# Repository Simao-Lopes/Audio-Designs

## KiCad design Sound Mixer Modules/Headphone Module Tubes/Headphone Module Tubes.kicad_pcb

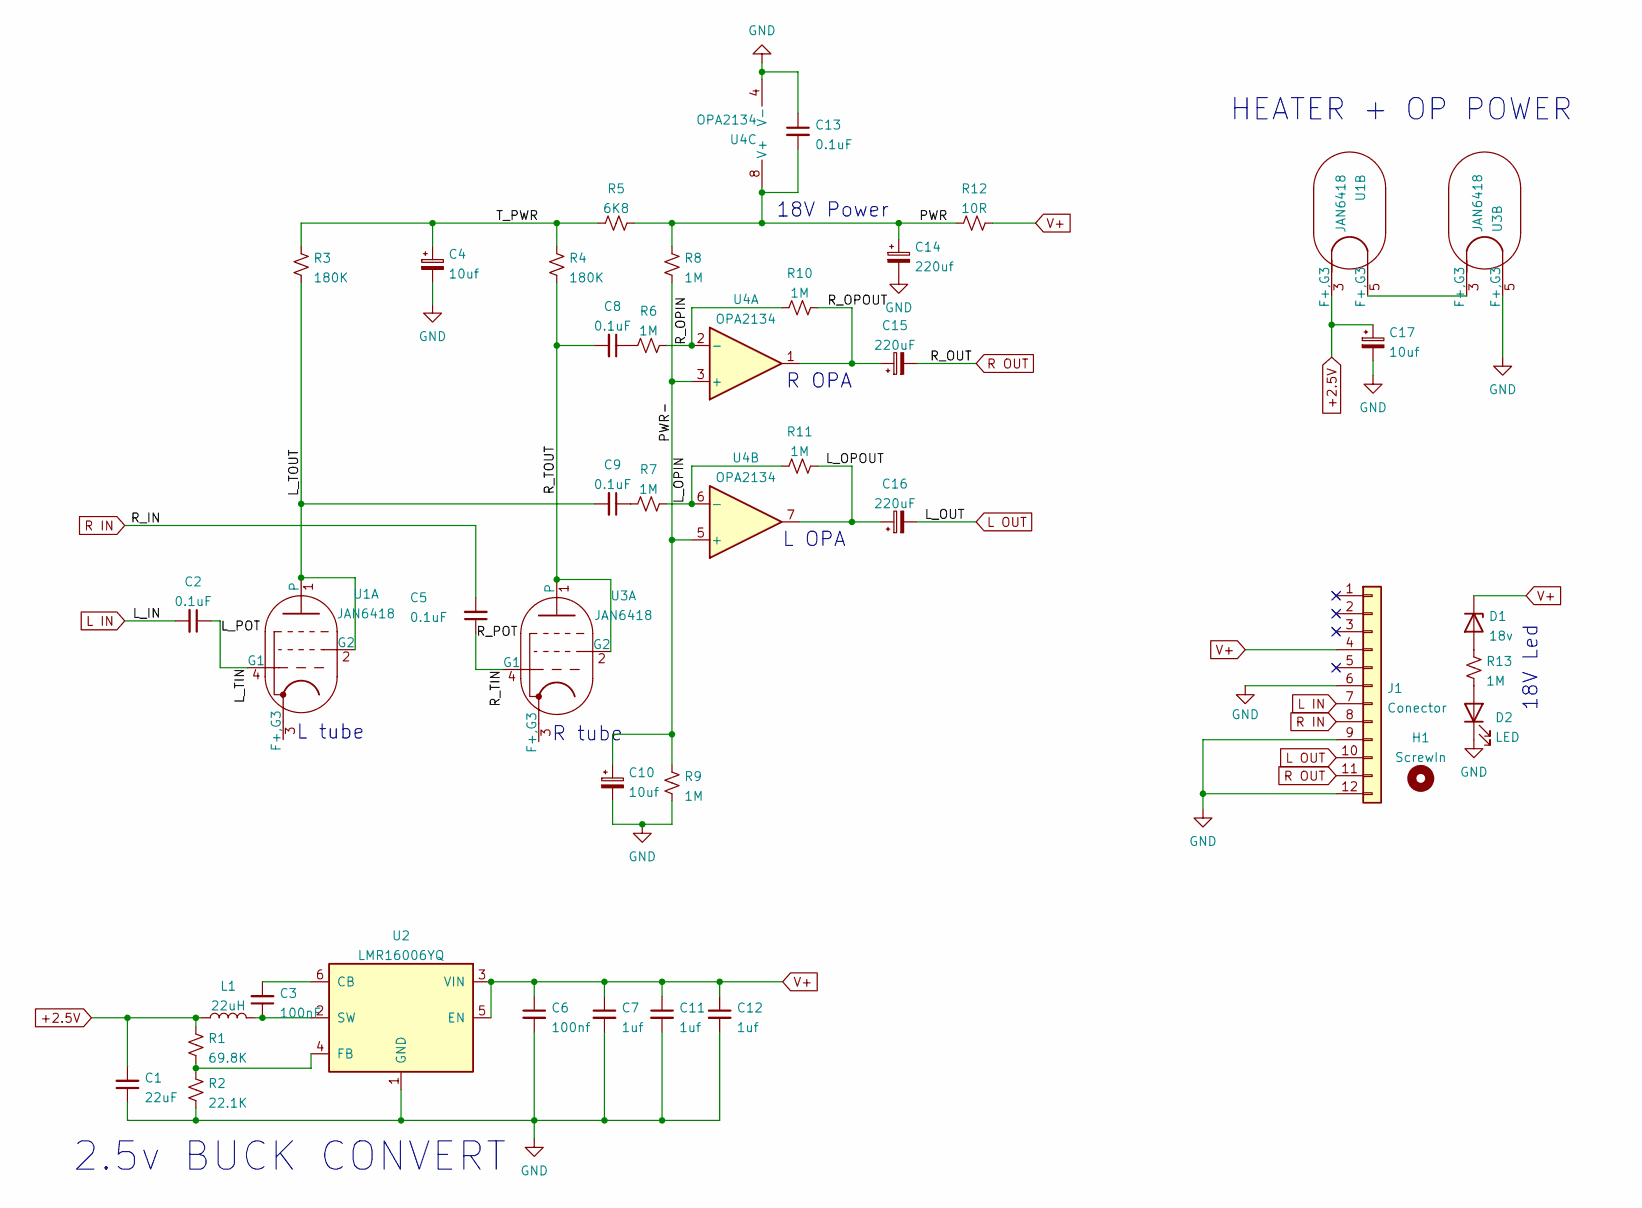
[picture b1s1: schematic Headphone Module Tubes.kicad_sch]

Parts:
C1: 22uF; C_0603_1608Metric_Pad1.08x0.95mm_HandSolder
C2, C5, C8, C9: 0.1uF; C_Rect_L7.2mm_W7.2mm_P5.00mm_FKS2_FKP2_MKS2_MKP2
C3: 100nF; C_0402_1005Metric_Pad0.74x0.62mm_HandSolder
C4, C10, C17: 10uf; CP_Radial_D5.0mm_P2.50mm
C6: 100nf; C_0603_1608Metric_Pad1.08x0.95mm_HandSolder
C7, C11, C12: 1uf; C_0603_1608Metric_Pad1.08x0.95mm_HandSolder
C13: 0.1uF; C_Rect_L7.2mm_W3.5mm_P5.00mm_FKS2_FKP2_MKS2_MKP2
C14: 220uf; CP_Radial_D10.0mm_P5.00mm_P7.50mm
C15, C16: 220uF; CP_Radial_D10.0mm_P5.00mm_P7.50mm
D1: 18v; D_1206_3216Metric_Pad1.42x1.75mm_HandSolder
D2: LED; LED_1206_3216Metric_Pad1.42x1.75mm_HandSolder
H1: ScrewIn; MountingHole_3.2mm_M3
J1: Conector; PinHeader_2x12_P2.54mm_Vertical
L1: 22uH; L_Bourns_SDR1806
R1: 69.8K; R_0402_1005Metric_Pad0.72x0.64mm_HandSolder
R2: 22.1K; R_0402_1005Metric_Pad0.72x0.64mm_HandSolder
R3, R4: 180K; R_1206_3216Metric_Pad1.30x1.75mm_HandSolder
R5: 6K8; R_1206_3216Metric_Pad1.30x1.75mm_HandSolder
R6, R7, R8, R9, R10, R11, R13: 1M; R_1206_3216Metric_Pad1.30x1.75mm_HandSolder
R12: 10R; R_1206_3216Metric_Pad1.30x1.75mm_HandSolder
U1, U3: JAN6418; Valve_Mini_Pentode_Linear
U2: LMR16006YQ; SOT-23-6
U4: OPA2134; DIP-8_W7.62mm

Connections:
+2.5V: C1.2, C17.1, L1.1, R1.1, U1.3 (F+,G3)
/L_OPIN: R7.2, R11.1, U4.6 (-)
/L_OPOUT: C16.1, R11.2, U4.7
/L_POT: C2.1, U1.4 (G1)
/L_TOUT: C9.2, R3.1, U1.1, U1.2 (G2)
/PWR: C13.2, C14.1, R5.1, R8.2, R12.2, U4.8 (V+)
/PWR-: C10.1, R8.1, R9.1, U4.3 (+), U4.5 (+)
/R_OPIN: R6.2, R10.1, U4.2 (-)
/R_OPOUT: C15.1, R10.2, U4.1
/R_POT: C5.1, U3.4 (G1)
/R_TOUT: C8.2, R4.1, U3.1, U3.2 (G2)
/T_PWR: C4.1, R3.2, R4.2, R5.2
L IN: C2.2, J1.7
L OUT: C16.2, J1.10
unnamed: C3.1, L1.2, U2.2 (SW)
unnamed: C3.2, U2.6 (CB)
unnamed: C8.1, R6.1
unnamed: C9.1, R7.1
unnamed: D1.2 (A), R13.2
unnamed: D2.2 (A), R13.1
unnamed: R1.2, R2.1, U2.4 (FB)
unnamed: U1.5 (F+,G3), U3.3 (F+,G3)
R IN: C5.2, J1.8
R OUT: C15.2, J1.11
V+: C6.1, C7.1, C11.1, C12.1, D1.1 (K), J1.4, R12.1, U2.3 (VIN), U2.5 (EN)

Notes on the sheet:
R tube
2.5v BUCK CONVERT
HEATER + OP POWER
L OPA
L tube
18V Led
R OPA
18V Power

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
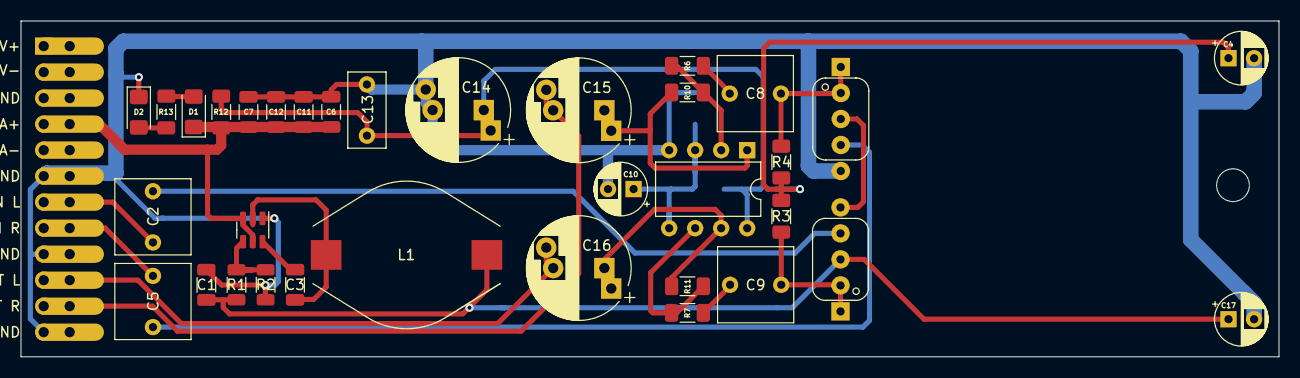
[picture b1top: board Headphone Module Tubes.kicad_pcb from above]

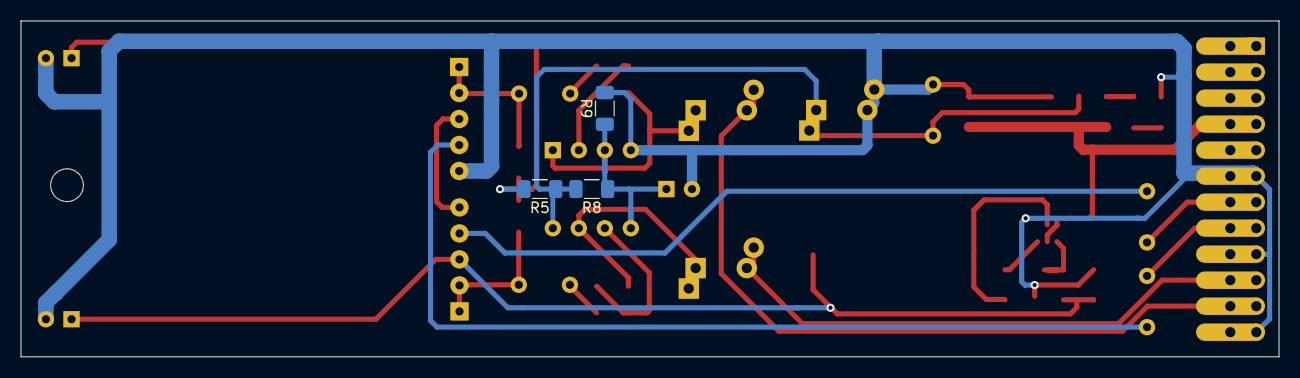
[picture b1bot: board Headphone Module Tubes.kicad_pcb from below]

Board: 2 copper layers, 122.9 x 32.8 mm, 39 parts (3 on the bottom side), 26 nets.

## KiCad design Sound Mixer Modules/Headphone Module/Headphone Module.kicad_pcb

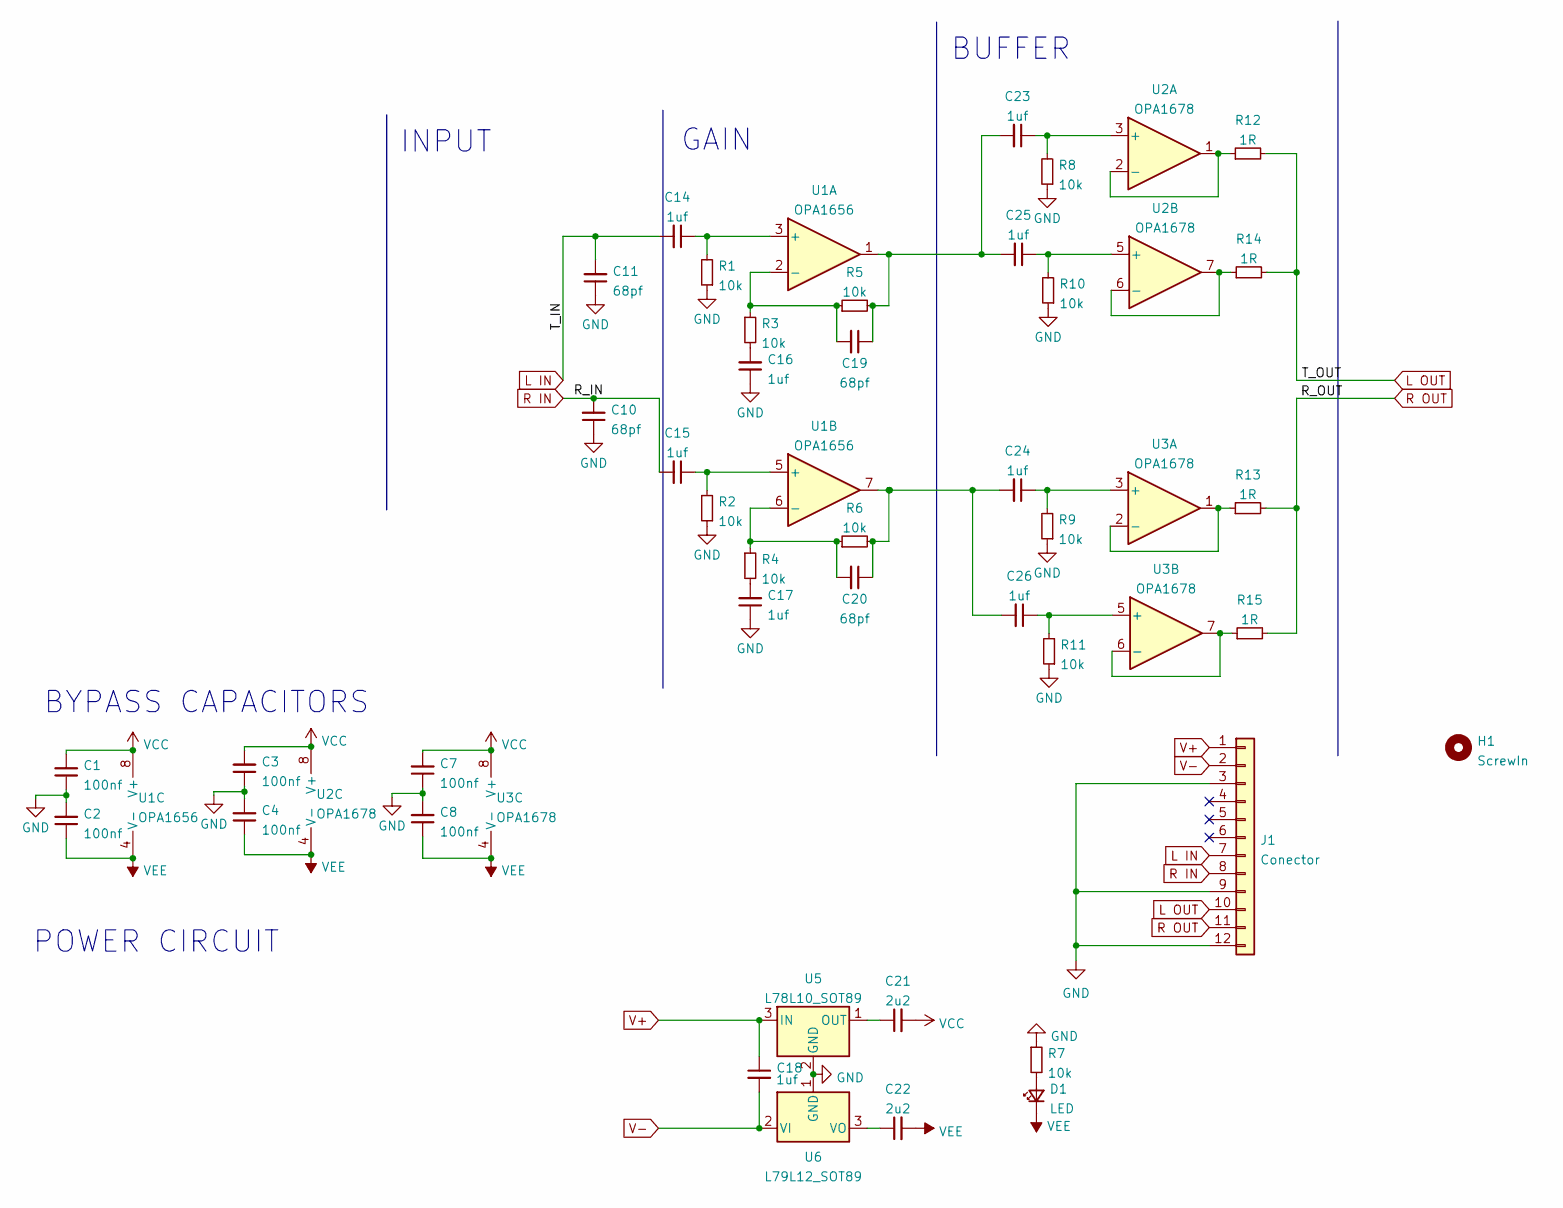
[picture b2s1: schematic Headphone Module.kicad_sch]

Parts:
C1, C2, C3, C4, C7, C8: 100nf; C_1206_3216Metric_Pad1.33x1.80mm_HandSolder
C10, C11, C19, C20: 68pf; C_1206_3216Metric_Pad1.33x1.80mm_HandSolder
C14, C15, C16, C17, C18, C23, C24, C25, C26: 1uf; C_1206_3216Metric_Pad1.33x1.80mm_HandSolder
C21, C22: 2u2; C_1206_3216Metric_Pad1.33x1.80mm_HandSolder
D1: LED; D_0201_0603Metric_Pad0.64x0.40mm_HandSolder
H1: ScrewIn; MountingHole_3.2mm_M3
J1: Conector; PinHeader_2x12_P2.54mm_Vertical
R1, R2, R3, R4, R5, R6, R7, R8, R9, R10, R11: 10k; R_0603_1608Metric_Pad0.98x0.95mm_HandSolder
R12, R13, R14, R15: 1R; R_0603_1608Metric_Pad0.98x0.95mm_HandSolder
U1: OPA1656; SOIC-8-1EP_3.9x4.9mm_P1.27mm_EP2.29x3mm
U2, U3: OPA1678; SOIC-8-1EP_3.9x4.9mm_P1.27mm_EP2.29x3mm
U5: L78L10_SOT89; SOT-89-3
U6: L79L12_SOT89; SOT-89-3

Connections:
GND: C1.1, C2.2, C3.1, C4.2, C7.1, C8.2, C10.1, C11.1, C16.1, C17.1, J1.3, J1.9, J1.12, R1.1, R2.1, R7.1, R8.1, R9.1, R10.1, R11.1, U5.2 (GND), U6.1 (GND)
L IN: C11.2, C14.2, J1.7
L OUT: J1.10, R12.2, R14.2
unnamed: C14.1, R1.2, U1.3 (+)
unnamed: C15.1, R2.2, U1.5 (+)
unnamed: C16.2, R3.2
unnamed: C17.2, R4.2
unnamed: C19.1, C23.2, C25.2, R5.2, U1.1
unnamed: C19.2, R3.1, R5.1, U1.2 (-)
unnamed: C20.1, R6.2, U1.7
unnamed: C20.2, R4.1, R6.1, U1.6 (-)
unnamed: C21.1, U5.1 (OUT)
unnamed: C22.1, U6.3 (VO)
unnamed: C23.1, R8.2, U2.3 (+)
unnamed: C24.1, R9.2, U3.3 (+)
unnamed: C24.2, C26.2
unnamed: C25.1, R10.2, U2.5 (+)
unnamed: C26.1, R11.2, U3.5 (+)
unnamed: D1.2 (A), R7.2
unnamed: R12.1, U2.1, U2.2 (-)
unnamed: R13.1, U3.1, U3.2 (-)
unnamed: R14.1, U2.6 (-), U2.7
unnamed: R15.1, U3.6 (-), U3.7
R IN: C10.2, C15.2, J1.8
R OUT: J1.11, R13.2, R15.2
V+: C18.1, J1.1, U5.3 (IN)
V-: C18.2, J1.2, U6.2 (VI)
VCC: C1.2, C3.2, C7.2, C21.2, U1.8 (V+), U2.8 (V+), U3.8 (V+)
VEE: C2.1, C4.1, C8.1, C22.2, D1.1 (K), U1.4 (V-), U2.4 (V-), U3.4 (V-)

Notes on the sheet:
INPUT
POWER CIRCUIT
GAIN
BUFFER
BYPASS CAPACITORS

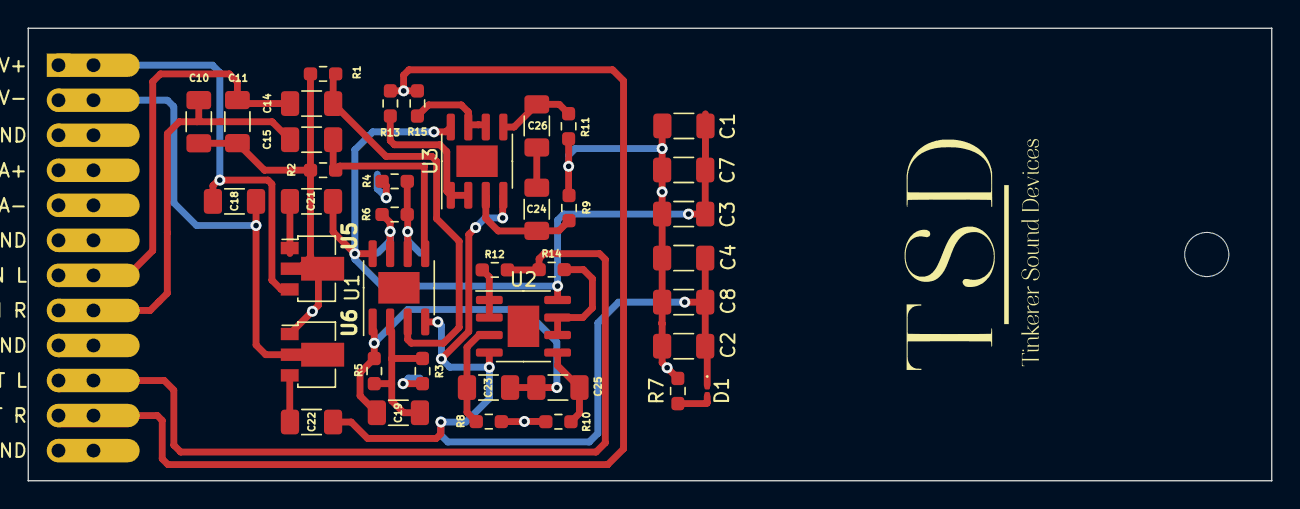
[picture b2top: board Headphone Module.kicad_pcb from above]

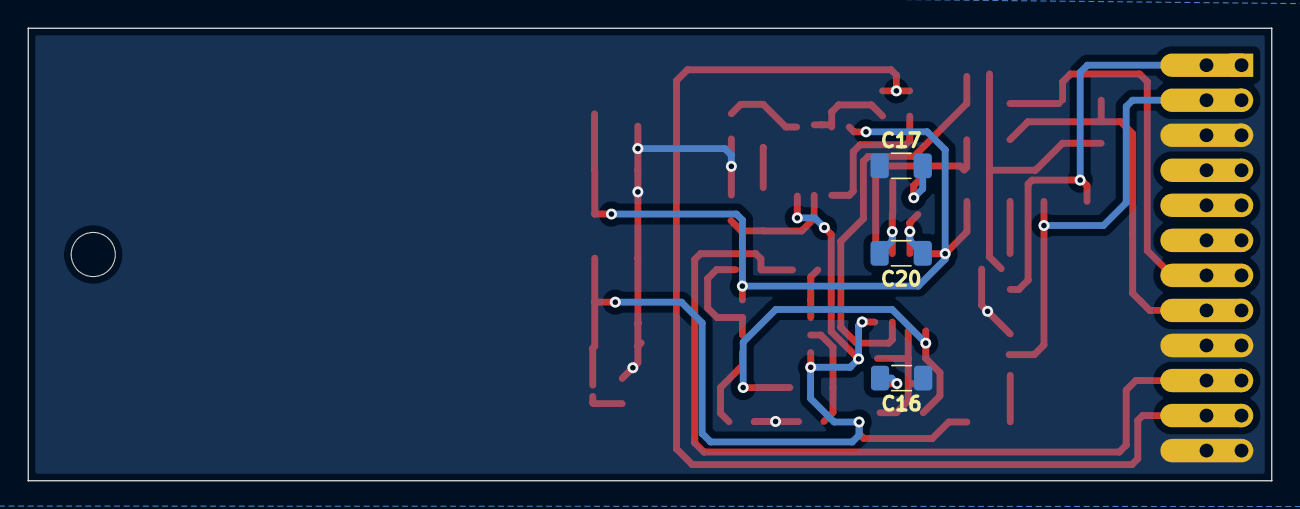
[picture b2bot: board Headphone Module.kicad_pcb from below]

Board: 2 copper layers, 90.1 x 32.8 mm, 44 parts (3 on the bottom side), 29 nets.

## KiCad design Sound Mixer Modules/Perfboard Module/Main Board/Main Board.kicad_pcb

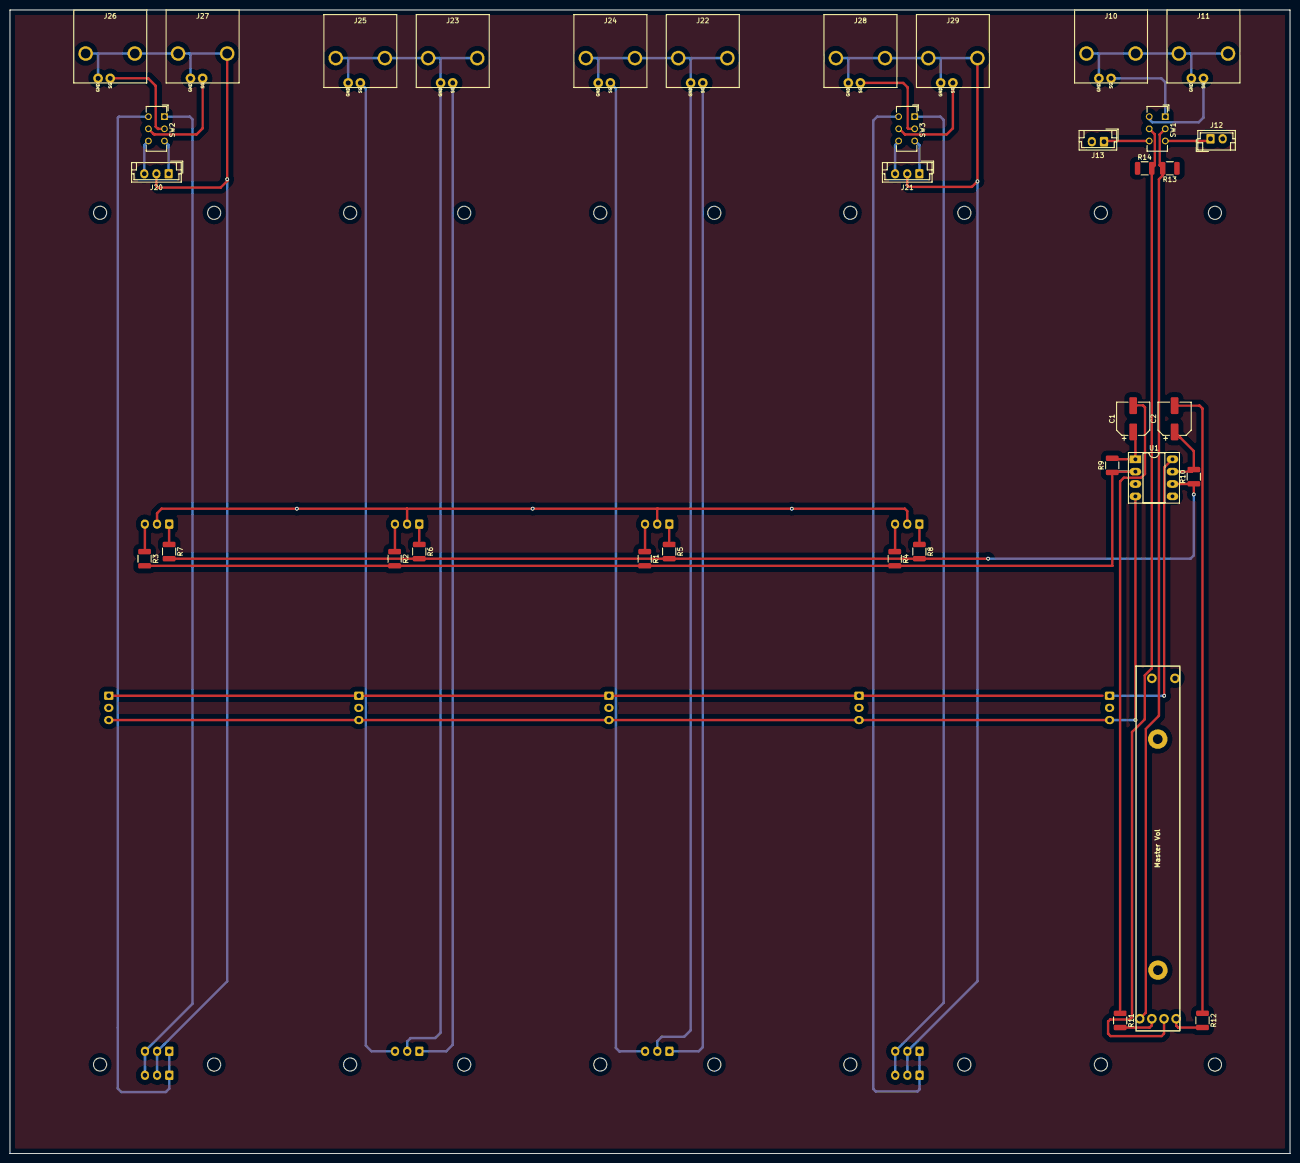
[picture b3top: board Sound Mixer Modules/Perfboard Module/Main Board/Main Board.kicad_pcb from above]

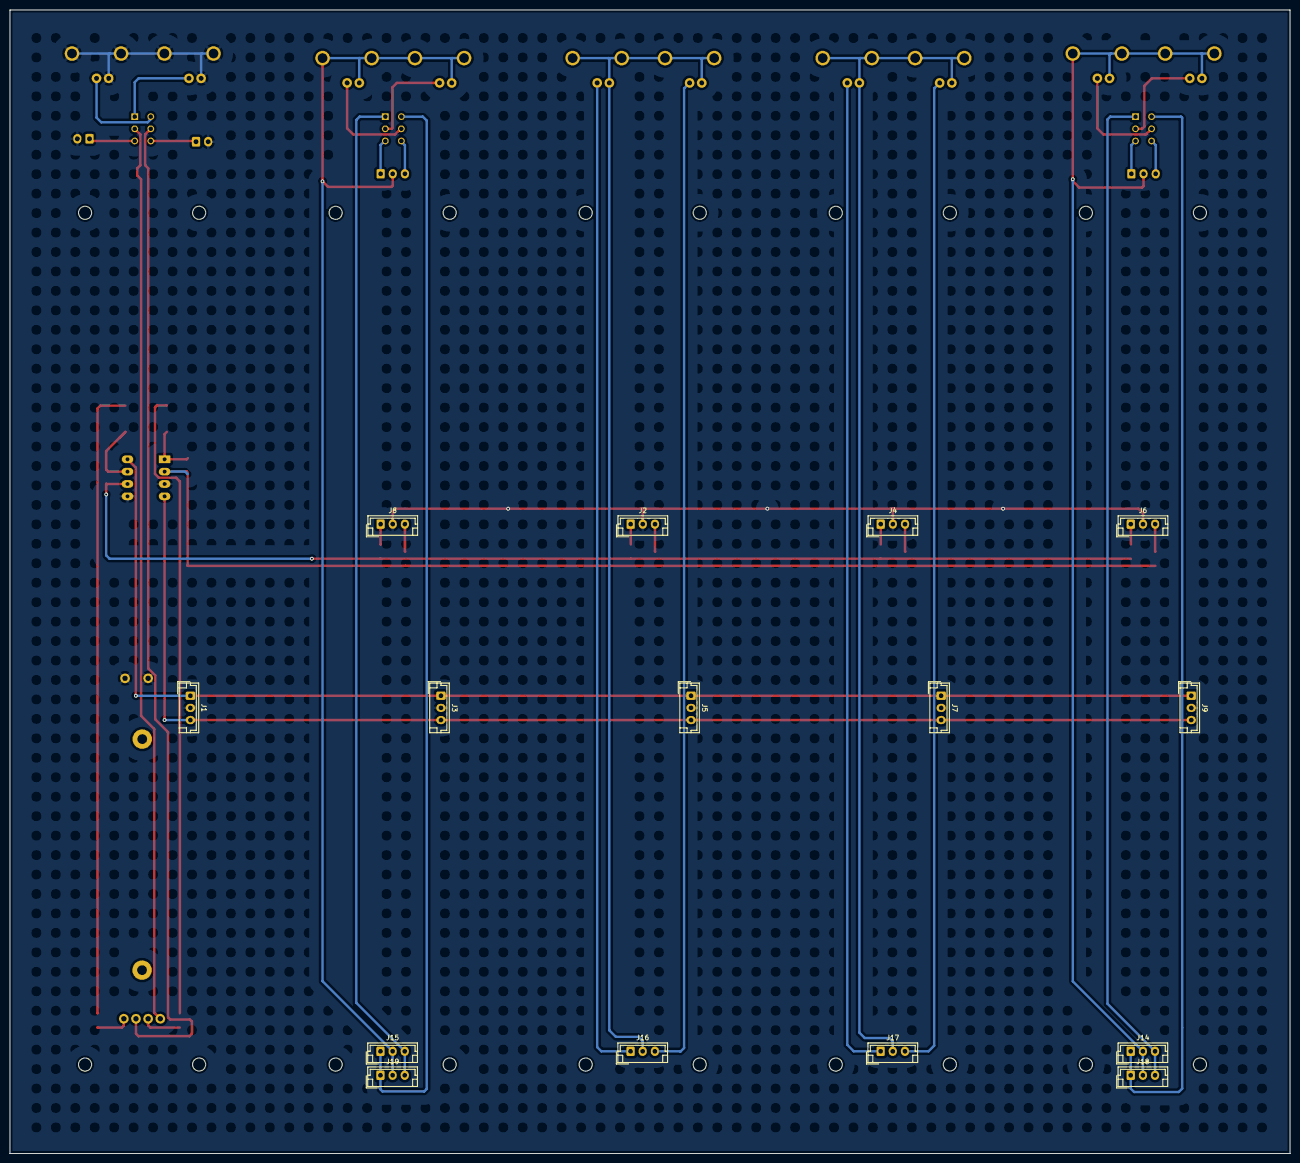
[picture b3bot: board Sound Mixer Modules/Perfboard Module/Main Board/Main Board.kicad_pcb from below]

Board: 2 copper layers, 263.2 x 235.1 mm, 50 parts (15 on the bottom side), 45 nets.

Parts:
C1, C2: 10Uf; CP_Elec_6.3x5.4_Nichicon
J1: Power mix; JST_EH_B3B-EH-A_1x03_P2.50mm_Vertical
J2: OUT1; JST_EH_B3B-EH-A_1x03_P2.50mm_Vertical
J3: Power1; JST_EH_B3B-EH-A_1x03_P2.50mm_Vertical
J4: OUT2; JST_EH_B3B-EH-A_1x03_P2.50mm_Vertical
J5: Power2; JST_EH_B3B-EH-A_1x03_P2.50mm_Vertical
J6: OUT3; JST_EH_B3B-EH-A_1x03_P2.50mm_Vertical
J7: Power3; JST_EH_B3B-EH-A_1x03_P2.50mm_Vertical
J8: OUT4; JST_EH_B3B-EH-A_1x03_P2.50mm_Vertical
J9: Power4; JST_EH_B3B-EH-A_1x03_P2.50mm_Vertical
J10: L_RCA; RCA PANEL 2PIN FOOTPRINT
J11, J22, J23, J24, J25, J26, J27, J28, J29: R_RCA; RCA PANEL 2PIN FOOTPRINT
J12: L_Amp; JST_EH_B2B-EH-A_1x02_P2.50mm_Vertical
J13: R_Amp; JST_EH_B2B-EH-A_1x02_P2.50mm_Vertical
J14: IN3; JST_EH_B3B-EH-A_1x03_P2.50mm_Vertical
J15: IN4; JST_EH_B3B-EH-A_1x03_P2.50mm_Vertical
J16: IN1; JST_EH_B3B-EH-A_1x03_P2.50mm_Vertical
J17: IN2; JST_EH_B3B-EH-A_1x03_P2.50mm_Vertical
J18: Phono In1; JST_EH_B3B-EH-A_1x03_P2.50mm_Vertical
J19: Phono In2; JST_EH_B3B-EH-A_1x03_P2.50mm_Vertical
J20: Phono out1; JST_EH_B3B-EH-A_1x03_P2.50mm_Vertical
J21: Phono out2; JST_EH_B3B-EH-A_1x03_P2.50mm_Vertical
R1, R2, R3, R4, R5, R6, R7, R8, R9, R10: 10K; R_1210_3225Metric
R11, R12: 100; R_1210_3225Metric
R13, R14: 15K; R_1210_3225Metric
RV1: Master Vol; ALPS RS60112
SW1: SW_DPDT_x2; SW_CuK_JS202011CQN_DPDT_Straight
SW2: IN3 SW; SW_CuK_JS202011CQN_DPDT_Straight
SW3: IN4 SW; SW_CuK_JS202011CQN_DPDT_Straight
U1: NE5532; DIP-8_W7.62mm_Socket_LongPads

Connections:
GND: J1.2, J2.2, J3.2, J4.2, J5.2, J6.2, J7.2, J8.2, J9.2, J10.2 (Ext), J11.2 (Ext), J12.2, J13.2, R13.1, R14.1, RV1.3, RV1.6, U1.3 (+), U1.5 (+)
L1: J2.3, R1.1
L2: J4.3, R2.1
L3: J6.3, R3.1
L4: J8.3, R4.1
unnamed: C1.1, R9.2, U1.1
unnamed: C1.2, R11.1
unnamed: C2.1, R10.2, U1.7
unnamed: C2.2, R12.1
unnamed: J1.1, J3.1, J5.1, J7.1, J9.1, U1.8 (V+)
unnamed: J1.3, J3.3, J5.3, J7.3, J9.3, U1.4 (V-)
unnamed: J10.1 (In), SW1.1 (A)
unnamed: J11.1 (In), SW1.4 (A)
unnamed: J12.1, SW1.3 (C)
unnamed: J13.1, SW1.6 (C)
unnamed: J14.1, J18.1, SW2.4 (A)
unnamed: J14.2, J18.2, J20.2, J26.2 (Ext), J27.2 (Ext)
unnamed: J14.3, J18.3, SW2.1 (A)
unnamed: J15.1, J19.1, SW3.4 (A)
unnamed: J15.2, J19.2, J21.2, J28.2 (Ext), J29.2 (Ext)
unnamed: J15.3, J19.3, SW3.1 (A)
unnamed: J16.1, J22.1 (In)
unnamed: J16.2, J22.2 (Ext)
unnamed: J16.3, J24.1 (In)
unnamed: J17.1, J23.1 (In)
unnamed: J17.2, J23.2 (Ext), J25.2 (Ext)
unnamed: J17.3, J25.1 (In)
unnamed: J20.1, SW2.3 (C)
unnamed: J20.3, SW2.6 (C)
unnamed: J21.1, SW3.3 (C)
unnamed: J21.3, SW3.6 (C)
unnamed: J26.1 (In), SW2.2 (B)
unnamed: J27.1 (In), SW2.5 (B)
unnamed: J28.1 (In), SW3.2 (B)
unnamed: J29.1 (In), SW3.5 (B)
unnamed: R1.2, R2.2, R3.2, R4.2, R9.1, U1.2 (-)
unnamed: R5.2, R6.2, R7.2, R8.2, R10.1, U1.6 (-)
unnamed: R11.2, RV1.1
unnamed: R12.2, RV1.4
unnamed: R13.2, RV1.2, SW1.2 (B)
unnamed: R14.2, RV1.5, SW1.5 (B)
R1: J2.1, R5.1
R2: J4.1, R6.1
R3: J6.1, R7.1
R4: J8.1, R8.1

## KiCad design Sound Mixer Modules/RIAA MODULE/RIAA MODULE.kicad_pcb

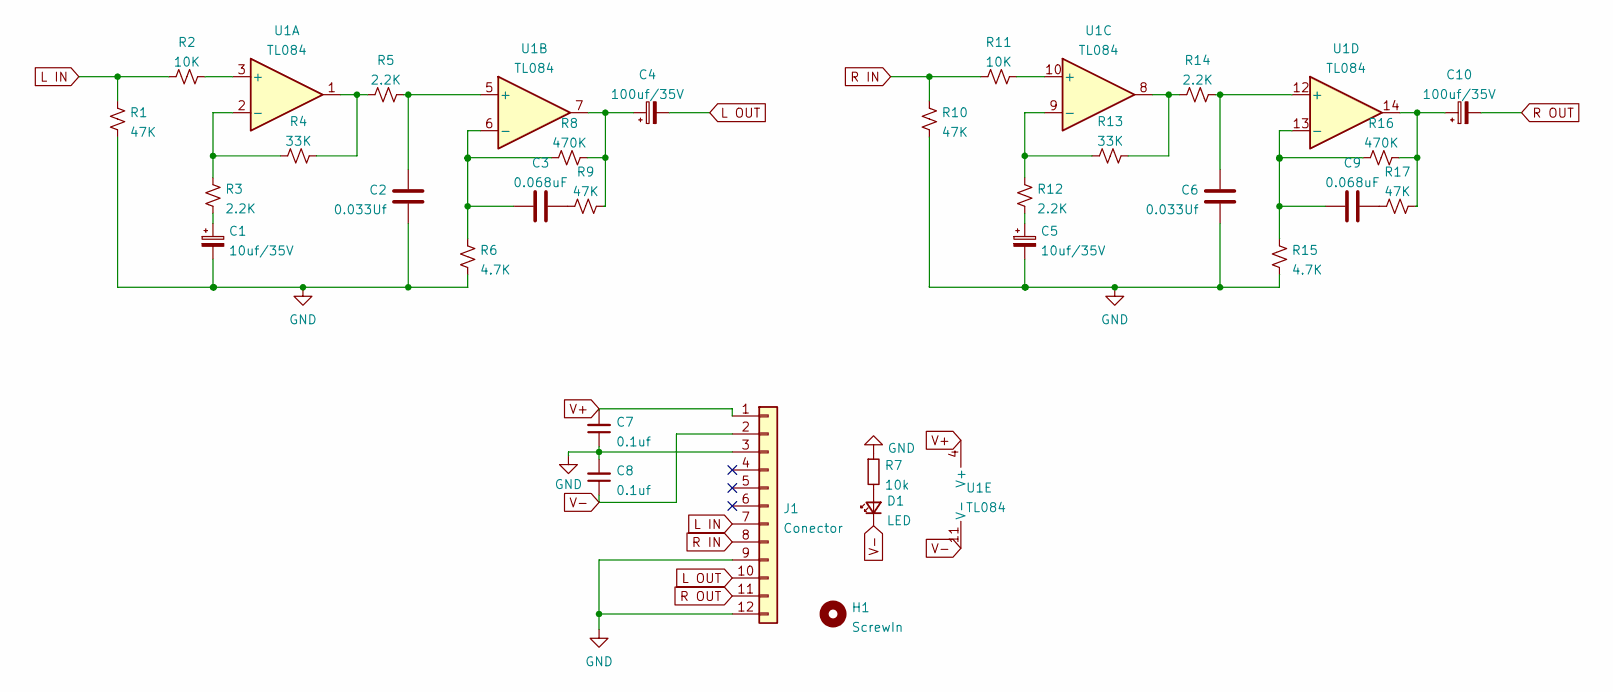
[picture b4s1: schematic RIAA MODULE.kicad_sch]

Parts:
C1, C5: 10uf/35V; CP_Elec_6.3x5.4_Nichicon
C2, C6: 0.033Uf; C_1206_3216Metric_Pad1.33x1.80mm_HandSolder
C3, C9: 0.068uF; C_1206_3216Metric_Pad1.33x1.80mm_HandSolder
C4, C10: 100uf/35V; CP_Elec_6.3x5.4_Nichicon
C7, C8: 0.1uf; C_1206_3216Metric_Pad1.33x1.80mm_HandSolder
D1: LED; D_0201_0603Metric_Pad0.64x0.40mm_HandSolder
H1: ScrewIn; MountingHole_3.2mm_M3
J1: Conector; PinHeader_2x12_P2.54mm_Vertical
R1, R9, R10, R17: 47K; R_1206_3216Metric
R2, R11: 10K; R_1206_3216Metric
R3, R5, R12, R14: 2.2K; R_1206_3216Metric
R4, R13: 33K; R_1206_3216Metric
R6, R15: 4.7K; R_1206_3216Metric
R7: 10k; R_1206_3216Metric
R8, R16: 470K; R_1206_3216Metric
U1: TL084; DIP-14_W7.62mm_Socket_LongPads

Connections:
GND: C2.2, C6.2, C7.1, C8.2, J1.3, J1.9, J1.12, R6.1, R7.1, R15.1
L IN: J1.7, R1.2, R2.1
L OUT: C4.2, J1.10
unnamed: C1.1, R3.1
unnamed: C1.2, R1.1
unnamed 5: C2.1, R5.1, U1.5 (+); also elsewhere on the board
unnamed: C3.1, R6.2
unnamed: C3.2, R9.2
unnamed 8: C4.1, R8.1, R9.1, U1.7; also elsewhere on the board
unnamed: C5.1, R12.1
unnamed: C5.2, R10.1
unnamed 11: C6.1, R14.1, U1.12 (+); also elsewhere on the board
unnamed: C9.1, R15.2
unnamed: C9.2, R17.2
unnamed 14: C10.1, R16.1, R17.1, U1.14; also elsewhere on the board
unnamed: D1.2 (A), R7.2
unnamed 16: R2.2, U1.3 (+); also elsewhere on the board
unnamed 17: R3.2, R4.2, U1.2 (-); also elsewhere on the board
unnamed 18: R4.1, R5.2, U1.1; also elsewhere on the board
unnamed 19: R8.2, U1.6 (-); also elsewhere on the board
unnamed 20: R11.2, U1.10 (+); also elsewhere on the board
unnamed 21: R12.2, R13.2, U1.9 (-); also elsewhere on the board
unnamed 22: R13.1, R14.2, U1.8; also elsewhere on the board
unnamed 23: R16.2, U1.13 (-); also elsewhere on the board
R IN: J1.8, R10.2, R11.1
R OUT: C10.2, J1.11
V+: C7.2, J1.1, U1.4 (V+); also elsewhere on the board
V-: C8.1, D1.1 (K), J1.2, U1.11 (V-); also elsewhere on the board

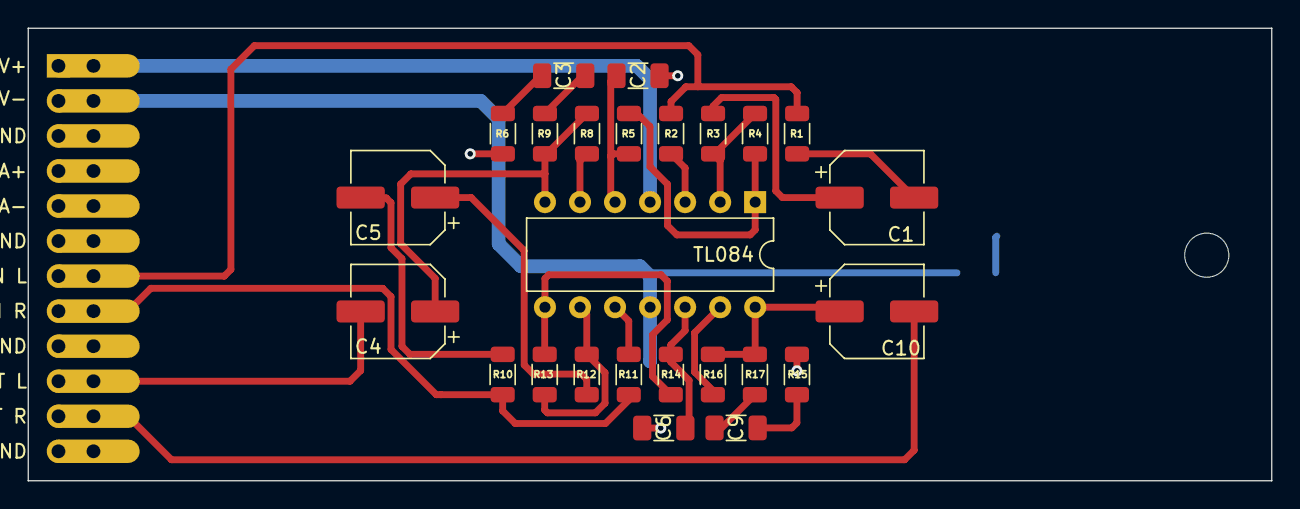
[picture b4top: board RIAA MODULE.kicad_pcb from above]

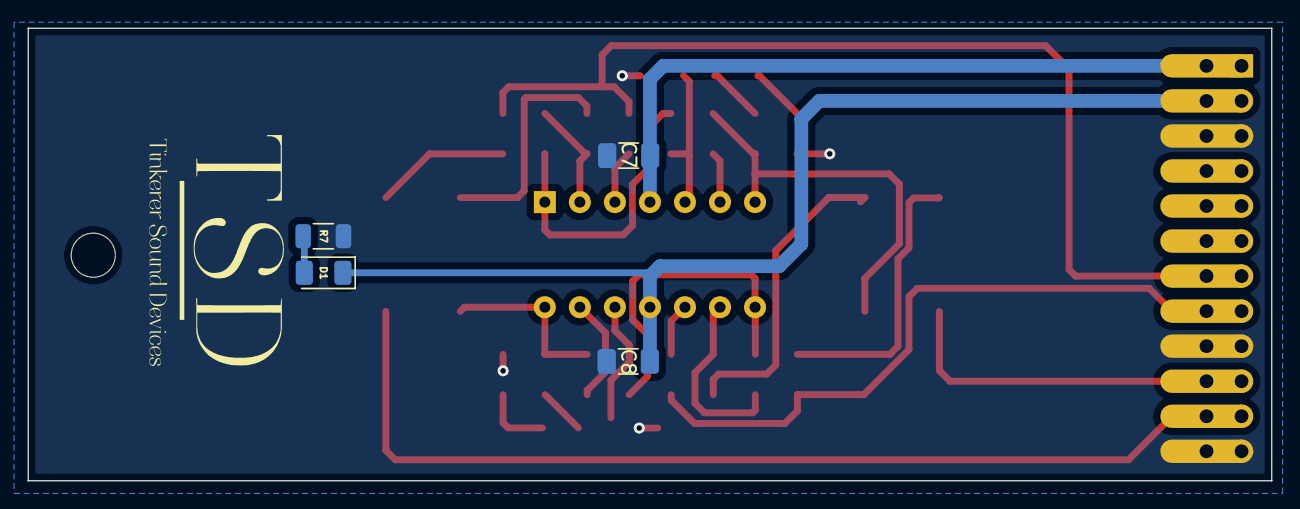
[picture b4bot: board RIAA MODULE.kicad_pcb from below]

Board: 2 copper layers, 90.1 x 32.8 mm, 31 parts (4 on the bottom side), 28 nets.

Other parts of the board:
TL084: TL084; DIP-14_W7.62mm

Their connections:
unnamed 5: TL084.5 (+); also elsewhere on the board
unnamed 8: TL084.7; also elsewhere on the board
unnamed 11: TL084.12 (+); also elsewhere on the board
unnamed 14: TL084.14; also elsewhere on the board
unnamed 16: TL084.3 (+); also elsewhere on the board
unnamed 17: TL084.2 (-); also elsewhere on the board
unnamed 18: TL084.1; also elsewhere on the board
unnamed 19: TL084.6 (-); also elsewhere on the board
unnamed 20: TL084.10 (+); also elsewhere on the board
unnamed 21: TL084.9 (-); also elsewhere on the board
unnamed 22: TL084.8; also elsewhere on the board
unnamed 23: TL084.13 (-); also elsewhere on the board
V+: TL084.4 (V+); also elsewhere on the board
V-: TL084.11 (V-); also elsewhere on the board

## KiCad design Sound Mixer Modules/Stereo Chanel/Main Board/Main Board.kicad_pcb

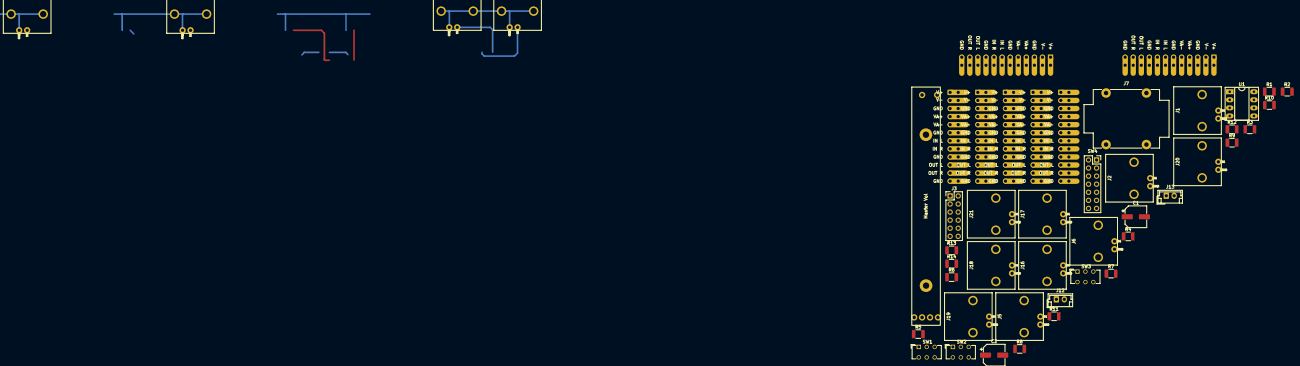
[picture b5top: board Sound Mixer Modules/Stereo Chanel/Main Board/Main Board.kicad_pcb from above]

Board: 2 copper layers, 47 parts (0 on the bottom side), 49 nets.

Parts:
C1, C2: 10Uf; CP_Elec_6.3x5.4_Nichicon
J1, J5, J20, J21: L In; RCA PANEL 2PIN FOOTPRINT
J2, J6, J22, J23: R In; RCA PANEL 2PIN FOOTPRINT
J3: Main Power; PinHeader_2x06_P2.54mm_Vertical
J4: Line 1; PinSocket_2x12_P2.54mm_Vertical
J7: AudioJack3; Jack_6.35mm_Neutrik_NMJ4HCD2_Horizontal
J8: Line 2; PinSocket_2x12_P2.54mm_Vertical
J9: Line 3; PinSocket_2x12_P2.54mm_Vertical
J10: L_RCA; RCA PANEL 2PIN FOOTPRINT
J11: R_RCA; RCA PANEL 2PIN FOOTPRINT
J12: L_Amp; JST_EH_B2B-EH-A_1x02_P2.50mm_Vertical
J13: R_Amp; JST_EH_B2B-EH-A_1x02_P2.50mm_Vertical
J14: Line 4; PinSocket_2x12_P2.54mm_Vertical
J15: RIAA 1; PinSocket_2x12_P2.54mm_Vertical
J16: Phono L1; RCA PANEL 2PIN FOOTPRINT
J17: Phono L2; RCA PANEL 2PIN FOOTPRINT
J18: Phono R1; RCA PANEL 2PIN FOOTPRINT
J19: Phono R2; RCA PANEL 2PIN FOOTPRINT
J24: RIAA 2; PinSocket_2x12_P2.54mm_Vertical
J25: HeadPhones Amp; PinSocket_2x12_P2.54mm_Vertical
R1, R2, R3, R4, R5, R6, R7, R8, R9, R10: 10K; R_1210_3225Metric
R11, R12: 100; R_1210_3225Metric
R13, R14: 15K; R_1210_3225Metric
RV1: Master Vol; ALPS RS60112
SW1: SW_DPDT_x2; SW_CuK_JS202011CQN_DPDT_Straight
SW2: IN3 SW; SW_CuK_JS202011CQN_DPDT_Straight
SW3: IN4 SW; SW_CuK_JS202011CQN_DPDT_Straight
SW4: SW_Rotary2x6; PinSocket_2x07_P2.54mm_Vertical
U1: NE5532; DIP-8_W7.62mm_Socket_LongPads

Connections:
GND: J1.2 (Ext), J2.2 (Ext), J3.3, J3.6, J3.7, J3.10, J4.3, J4.6, J4.9, J4.12, J5.2 (Ext), J6.2 (Ext), J7.S, J8.3, J8.6, J8.9, J8.12, J9.3, J9.6, J9.9, J9.12, J10.2 (Ext), J11.2 (Ext), J12.2, J13.2, J14.3, J14.6, J14.9, J14.12, J15.3, J15.6, J15.12, J20.2 (Ext), J21.2 (Ext), J22.2 (Ext), J23.2 (Ext), J24.3, J24.6, J24.12, J25.3, J25.6, J25.9, J25.12, R13.1, R14.1, RV1.3, RV1.6, U1.3 (+), U1.5 (+)
L1: J4.10, R1.1, SW4.1
L2: J8.10, R2.1, SW4.2
L3: J9.10, R3.1, SW4.3
L4: J14.10, R4.1, SW4.4
Mix1 L: J9.7, SW3.2 (B)
Mix1 R: J9.8, SW3.5 (B)
Mix2 R: J14.8, SW2.5 (B)
unnamed: C1.1, R9.2, U1.1
unnamed: C1.2, R11.1
unnamed: C2.1, R10.2, U1.7
unnamed: C2.2, R12.1
unnamed: J1.1 (In), J4.7
unnamed: J2.1 (In), J4.8
unnamed: J5.1 (In), J8.7
unnamed: J6.1 (In), J8.8
unnamed: J10.1 (In), SW1.1 (A)
unnamed: J11.1 (In), SW1.4 (A)
unnamed: J12.1, SW1.3 (C)
unnamed: J13.1, SW1.6 (C)
unnamed: J20.1 (In), SW3.1 (A)
unnamed: J22.1 (In), SW3.4 (A)
unnamed: J23.1 (In), SW2.4 (A)
unnamed: R1.2, R2.2, R3.2, R4.2, R9.1, U1.2 (-)
unnamed: R5.2, R6.2, R7.2, R8.2, R10.1, U1.6 (-)
unnamed: R11.2, RV1.1
unnamed: R12.2, RV1.4
unnamed: R14.2, RV1.5, SW1.5 (B)
OUT L: R13.2, RV1.2, SW1.2 (B)
Phones L: J25.7, SW4.13
Phones Out L: J7.T, J25.10
Phones R: J25.8, SW4.14
Phono GND 1: J15.9, J16.2 (Ext), J18.2 (Ext)
Phono GND 2: J17.2 (Ext), J19.2 (Ext), J24.9
Phono L 1: J15.7, J16.1 (In)
Phono L 2: J17.1 (In), J24.7
Phono L Out 1: J15.10, SW3.3 (C)
Phono R 1: J15.8, J18.1 (In)
Phono R 2: J19.1 (In), J24.8
Phono R Out 1: J15.11, SW3.6 (C)
Phono R Out 2: J24.11, SW2.6 (C)
R1: J4.11, R5.1, SW4.7
R2: J8.11, R6.1, SW4.8
R3: J9.11, R7.1, SW4.9
R4: J14.11, R8.1, SW4.10
V AUX+: J3.4, J3.9, J4.4, J8.4, J9.4, J14.4, J15.4, J24.4, J25.4
V AUX-: J3.5, J3.8, J4.5, J8.5, J9.5, J14.5, J15.5, J24.5, J25.5
V+: J3.1, J3.12, J4.1, J8.1, J9.1, J14.1, J15.1, J24.1, J25.1, U1.8 (V+)
V-: J3.2, J3.11, J4.2, J8.2, J9.2, J14.2, J15.2, J24.2, J25.2, U1.4 (V-)
